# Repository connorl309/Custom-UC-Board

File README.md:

# Custom 32-bit ARM Microcontroller Board
This project is my attempt at designing and fabricating a custom PCB for the [TMPM46BF10FG](https://www.mouser.com/ProductDetail/Toshiba/TMPM46BF10FG?qs=wd5RIQLrsJi6ktKViwPiDg%3D%3D), developed by Toshiba. It is rich in features, and while not a very beginner friendly chip to work with, satisfies a lot of my requirements in finding a great UC to use.

A few references for the microcontroller can be found below.  

## The Board
The board itself is originally starting out as a 2-layer board. I will be trying to be aware of EMI and signal degradation effects, but due to me being a student, I don't have tons of cash to throw around on multilayer boards if I mess something up.  
A few of my core goals are as follows.

* Ease of access to GPIO and special function pins: not restricting their access or usage.
* Ease of use for the board overall: accessibility of peripherals, pin input and outputs, and uploading programs to the UC.
* Smart layout choices: can an end user easily identify their required pins, and understand board functionality.
* Does it feel *good* to use? (I hope so!)

This is my first foray into real PCB design, and I'm excited to display my progress on this project here.

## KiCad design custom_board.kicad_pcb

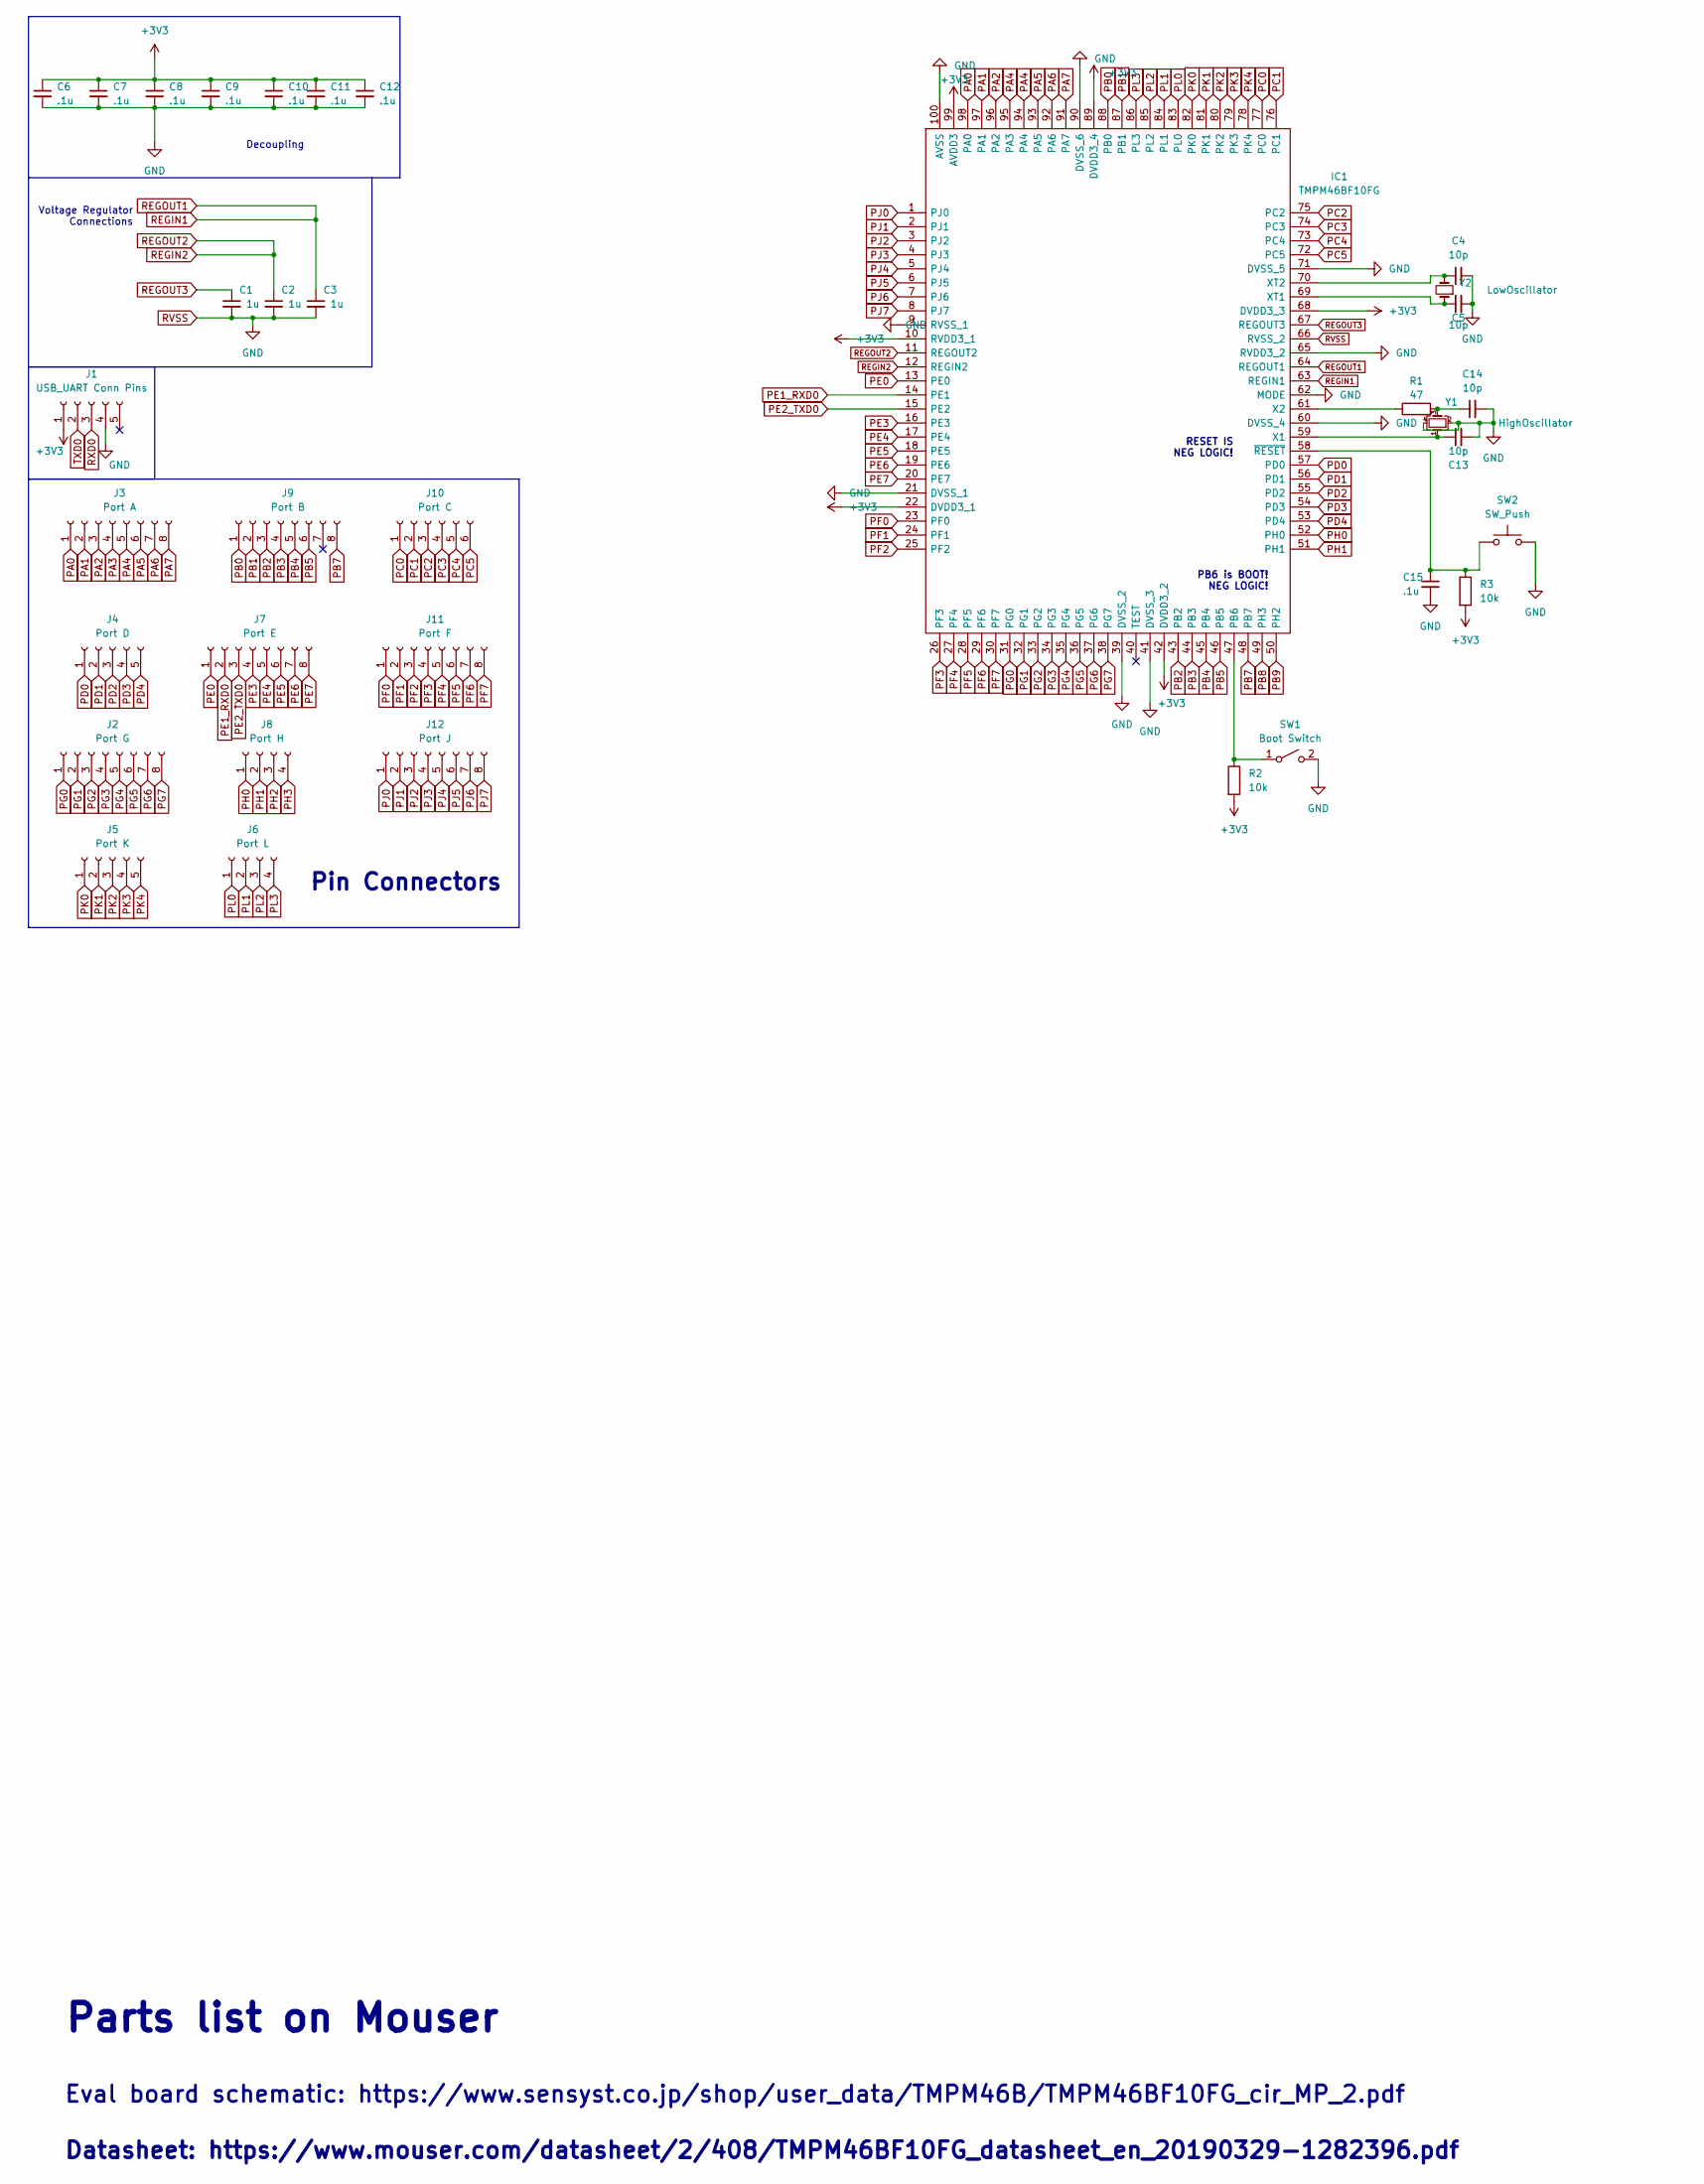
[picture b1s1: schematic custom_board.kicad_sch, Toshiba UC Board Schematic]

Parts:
C1, C2, C3: 1u; C_0805_2012Metric
C4, C5, C13, C14: 10p; C_0805_2012Metric
C6, C7, C8, C9, C10, C11, C12, C15: .1u; C_0805_2012Metric
IC1: TMPM46BF10FG; TMPM_Custom_Footprint; Mouser Part Number 757-TMPM46BF10FG
J1: USB_UART Conn Pins; PinSocket_1x05_P2.54mm_Horizontal
J2: Port G; PinSocket_1x08_P2.54mm_Vertical
J3: Port A; PinSocket_1x08_P2.54mm_Vertical
J4: Port D; PinSocket_1x05_P2.54mm_Vertical
J5: Port K; PinSocket_1x05_P2.54mm_Vertical
J6: Port L; PinSocket_1x04_P2.54mm_Vertical
J7: Port E; PinSocket_1x08_P2.54mm_Vertical
J8: Port H; PinSocket_1x04_P2.54mm_Vertical
J9: Port B; PinSocket_1x08_P2.54mm_Vertical
J10: Port C; PinSocket_1x06_P2.54mm_Vertical
J11: Port F; PinSocket_1x08_P2.54mm_Vertical
J12: Port J; PinSocket_1x08_P2.54mm_Vertical
R1: 47; R_0805_2012Metric_Pad1.20x1.40mm_HandSolder
R2, R3: 10k; R_0805_2012Metric_Pad1.20x1.40mm_HandSolder
SW1: Boot Switch; SW_DIP_SPSTx01_Slide_9.78x4.72mm_W8.61mm_P2.54mm
SW2: SW_Push; Push_E-Switch_KS01Q01
Y1: HighOscillator; Crystal_SMD_Abracon_ABM10-4Pin_2.5x2.0mm
Y2: LowOscillator; Crystal_SMD_EuroQuartz_EQ161-2Pin_3.2x1.5mm_HandSoldering

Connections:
+3V3: C6.1, C7.1, C8.1, C9.1, C10.1, C11.1, C12.1, IC1.10 (RVDD3_1), IC1.22 (DVDD3_1), IC1.42 (DVDD3_2), IC1.68 (DVDD3_3), IC1.89 (DVDD3_4), IC1.99 (AVDD3), J1.1, R2.2, R3.2
unnamed: C4.1, IC1.70 (XT2), Y2.2
unnamed: C5.1, IC1.69 (XT1), Y2.1
unnamed: C13.1, IC1.59 (X1), Y1.1
unnamed: C14.1, R1.2, Y1.3
unnamed: IC1.47 (PB6), R2.1, SW1.1 (A)
unnamed: C15.1, IC1.58 (~RESET), R3.1, SW2.1
unnamed: IC1.61 (X2), R1.1
PA0: IC1.98 (PA0), J3.1
PA1: IC1.97 (PA1), J3.2
PA2: IC1.96 (PA2), J3.3
PA3: J3.4
PA4: IC1.94 (PA4), IC1.95 (PA3), J3.5
PA5: IC1.93 (PA5), J3.6
PA6: IC1.92 (PA6), J3.7
PA7: IC1.91 (PA7), J3.8
PB0: IC1.88 (PB0), J9.1
PB1: IC1.87 (PB1), J9.2
PB2: IC1.43 (PB2), J9.3
PB3: IC1.44 (PB3), J9.4
PB4: IC1.45 (PB4), J9.5
PB5: IC1.46 (PB5), J9.6
PB7: IC1.48 (PB7), J9.8
PB8: IC1.49 (PH3)
PB9: IC1.50 (PH2)
PC0: IC1.77 (PC0), J10.1
PC1: IC1.76 (PC1), J10.2
PC2: IC1.75 (PC2), J10.3
PC3: IC1.74 (PC3), J10.4
PC4: IC1.73 (PC4), J10.5
PC5: IC1.72 (PC5), J10.6
PD0: IC1.57 (PD0), J4.1
PD1: IC1.56 (PD1), J4.2
PD2: IC1.55 (PD2), J4.3
PD3: IC1.54 (PD3), J4.4
PD4: IC1.53 (PD4), J4.5
PE0: IC1.13 (PE0), J7.1
PE1_RXD0: IC1.14 (PE1), J7.2
PE2_TXD0: IC1.15 (PE2), J7.3
PE3: IC1.16 (PE3), J7.4
PE4: IC1.17 (PE4), J7.5
PE5: IC1.18 (PE5), J7.6
PE6: IC1.19 (PE6), J7.7
PE7: IC1.20 (PE7), J7.8
PF0: IC1.23 (PF0), J11.1
PF1: IC1.24 (PF1), J11.2
PF2: IC1.25 (PF2), J11.3
PF3: IC1.26 (PF3), J11.4
PF4: IC1.27 (PF4), J11.5
PF5: IC1.28 (PF5), J11.6
PF6: IC1.29 (PF6), J11.7
PF7: IC1.30 (PF7), J11.8
PG0: IC1.31 (PG0), J2.1
PG1: IC1.32 (PG1), J2.2
PG2: IC1.33 (PG2), J2.3
PG3: IC1.34 (PG3), J2.4
PG4: IC1.35 (PG4), J2.5
PG5: IC1.36 (PG5), J2.6
PG6: IC1.37 (PG6), J2.7
PG7: IC1.38 (PG7), J2.8
PH0: IC1.52 (PH0), J8.1
PH1: IC1.51 (PH1), J8.2
PH2: J8.3
PH3: J8.4
PJ0: IC1.1 (PJ0), J12.1
PJ1: IC1.2 (PJ1), J12.2
PJ2: IC1.3 (PJ2), J12.3
PJ3: IC1.4 (PJ3), J12.4
PJ4: IC1.5 (PJ4), J12.5
PJ5: IC1.6 (PJ5), J12.6
PJ6: IC1.7 (PJ6), J12.7
PJ7: IC1.8 (PJ7), J12.8
PK0: IC1.82 (PK0), J5.1
PK1: IC1.81 (PK1), J5.2
PK2: IC1.80 (PK2), J5.3
PK3: IC1.79 (PK3), J5.4
PK4: IC1.78 (PK4), J5.5
PL0: IC1.83 (PL0), J6.1
PL1: IC1.84 (PL1), J6.2
PL2: IC1.85 (PL2), J6.3
PL3: IC1.86 (PL3), J6.4
REGIN1: C3.1, IC1.63 (REGIN1), IC1.64 (REGOUT1)
REGIN2: C2.1, IC1.11 (REGOUT2), IC1.12 (REGIN2)
REGOUT3: C1.1, IC1.67 (REGOUT3)
RVSS: C1.2, C2.2, C3.2, C4.2, C5.2, C6.2, C7.2, C8.2, C9.2, C10.2, C11.2, C12.2, C13.2, C14.2, C15.2, IC1.9 (RVSS_1), IC1.21 (DVSS_1), IC1.39 (DVSS_2), IC1.41 (DVSS_3), IC1.60 (DVSS_4), IC1.62 (MODE), IC1.65 (RVDD3_2), IC1.66 (RVSS_2), IC1.71 (DVSS_5), IC1.90 (DVSS_6), IC1.100 (AVSS), J1.4, SW1.2 (B), SW2.2, Y1.2, Y1.4
RXD0: J1.3
TXD0: J1.2

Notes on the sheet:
Pin Connectors
Datasheet: https://www.mouser.com/datasheet/2/408/TMPM46BF10FG_datasheet_en_20190329-1282396.pdf
PB6 is BOOT! NEG LOGIC!
Parts list on Mouser
RESET IS NEG LOGIC!
Eval board schematic: https://www.sensyst.co.jp/shop/user_data/TMPM46B/TMPM46BF10FG_cir_MP_2.pdf
Voltage Regulator Connections
Decoupling

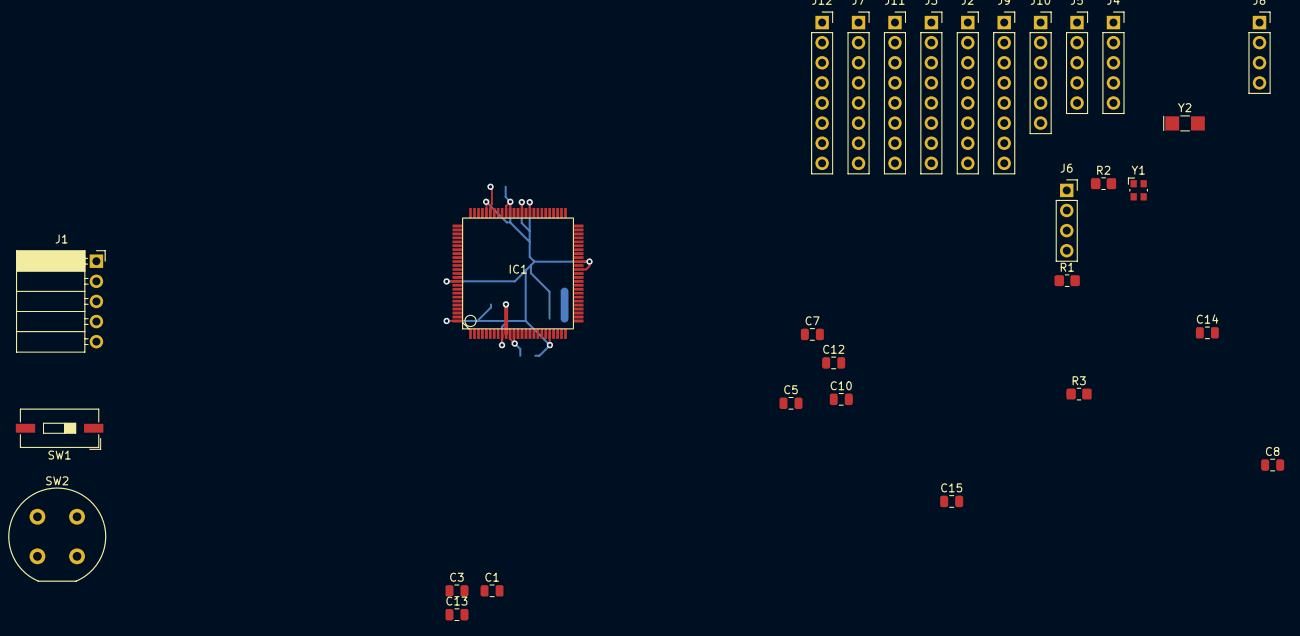
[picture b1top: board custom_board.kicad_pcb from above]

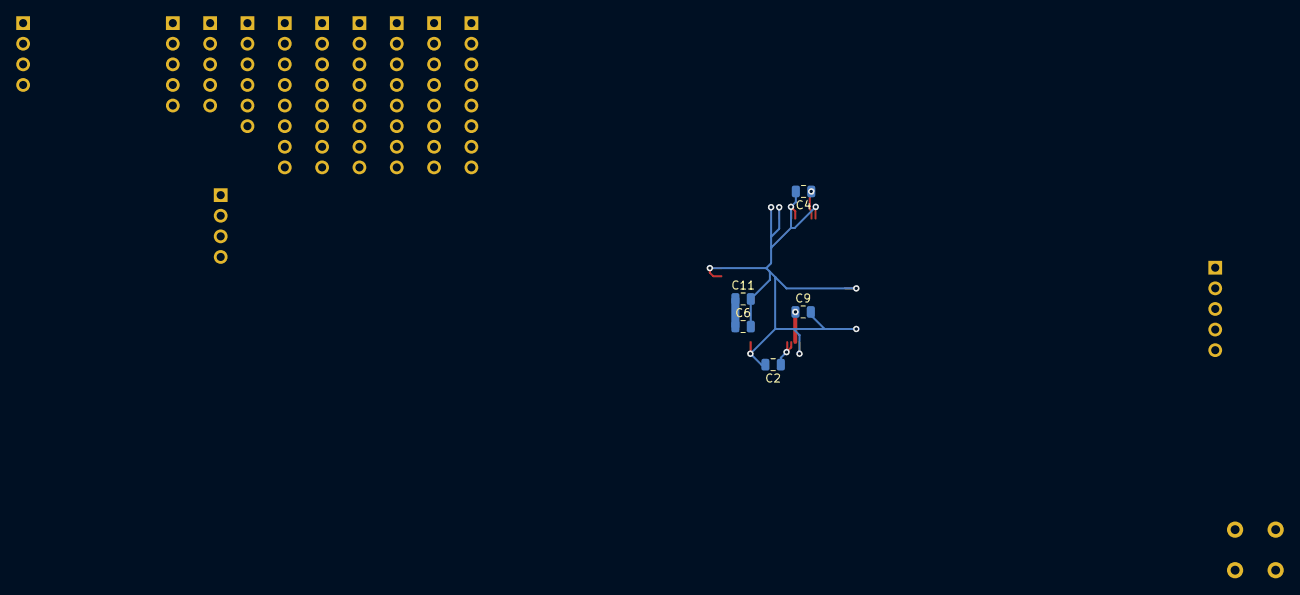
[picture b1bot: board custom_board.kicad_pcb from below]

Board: 2 copper layers, 35 parts (5 on the bottom side), 80 nets.

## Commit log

2022-10-19 init
2022-10-19 gitignore
2022-10-19 Updating footprint stuff
2022-10-19 REALLY updated footyprint now
2022-10-19 working on pin connections
2022-10-20 footprint
2022-10-20 Working on hardware interfaces
2022-10-20 added firmware
